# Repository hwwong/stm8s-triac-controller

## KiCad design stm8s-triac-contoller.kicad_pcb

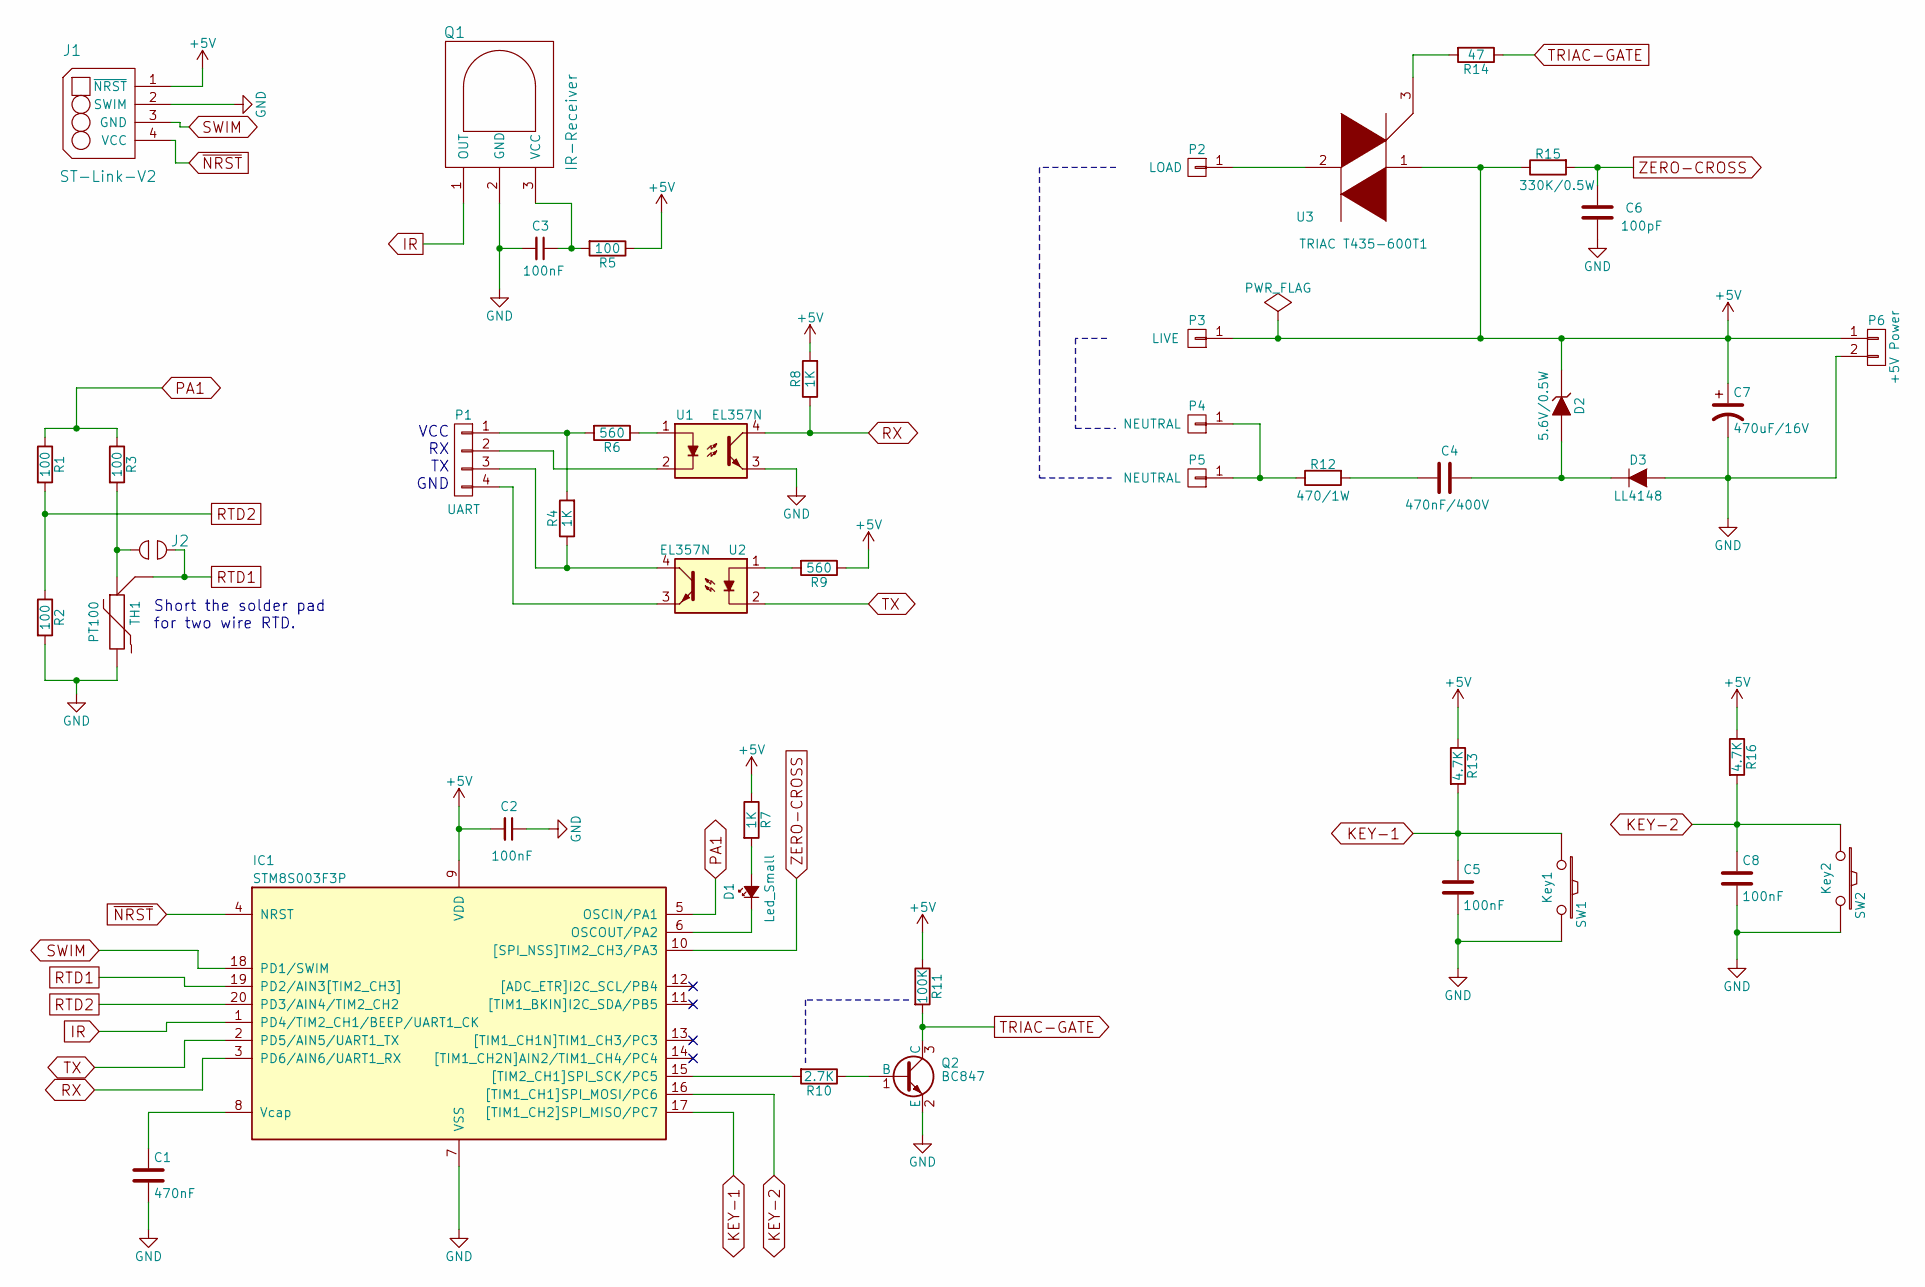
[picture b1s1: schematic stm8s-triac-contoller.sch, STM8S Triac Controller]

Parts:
C1: 470nF; C_0805
C2, C3, C5, C8: 100nF; C_0805
C4: 470nF/400V; C_Rect_L18_W11_H19_P15
C6: 100pF; C_0805
C7: 470uF/16V; C_Radial_D8_L11.5_P3.5
D1: Led_Small; LED-3MM
D2: 5.6V/0.5W; SOD-80
D3: LL4148; SOD-80
IC1: STM8S003F3P; TSSOP-20_4.4x6.5mm_Pitch0.65mm
J1: ST-Link-V2; Pin_Header_Straight_1x04
J2: Solder-Jumper-2; PAD-JUMPER-2-NO_YES_SILK
P1: UART; Pin_Header_Straight_1x04
P2: LOAD; SolderWirePad_single_1-2mmDrill
P3: LIVE; SolderWirePad_single_1-2mmDrill
P4, P5: NEUTRAL; SolderWirePad_single_1-2mmDrill
P6: +5V Power; Pin_Header_Straight_1x02
Q1: IR-Receiver; PNA460XM
Q2: BC847; SOT-23
R1, R2, R3, R5: 100; R_0805
R4, R7, R8: 1K; R_0805
R6, R9: 560; R_0805
R10: 2.7K; R_0805
R11: 100K; R_0805
R12: 470/1W; Resistor_Vertical_RM5mm
R13, R16: 4.7K; R_0805
R14: 47; R_0805
R15: 330K/0.5W; Resistor_Horizontal_RM10mm
SW1: Key1; TACTILE-PTH
SW2: Key2; TACTILE-PTH
TH1: PT100; TerminalBlock_Pheonix_MKDS1.5-3pol
U1, U2: EL357N; Optocoupler_SMD_HandSoldering_KPC357_LTV35x_PC357_SingleCha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
U3: TRIAC T435-600T1; TO-220_Neutral123_Vertical_LargePads

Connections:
+5V: C2.2, C7.1, D2.1 (K), IC1.9 (VDD), J1.1 (~NRST), P3.1, P6.1, R5.1, R7.1, R8.2, R9.1, R11.1, R13.1, R15.1, R16.1, U3.1
GND: C1.2, C2.1, C3.2, C5.2, C6.2, C7.2, C8.2, D3.2 (A), IC1.7 (VSS), J1.2 (SWIM), P6.2, Q1.2 (GND), Q2.2 (E), R2.2, SW1.2, SW2.2, TH1.3, U1.3
IR: IC1.1 (PD4/TIM2_CH1/BEEP/UART1_CK), Q1.1 (OUT)
KEY-1: C5.1, IC1.17 ([TIM1_CH2]SPI_MISO/PC7), R13.2, SW1.1
KEY-2: C8.1, IC1.16 ([TIM1_CH1]SPI_MOSI/PC6), R16.2, SW2.1
unnamed: C1.1, IC1.8 (Vcap)
unnamed: C3.1, Q1.3 (VCC), R5.2
unnamed: C4.1, D2.2 (A), D3.1 (K)
unnamed: C4.2, R12.2
unnamed: D1.1 (K), IC1.6 (OSCOUT/PA2)
unnamed: D1.2 (A), R7.2
unnamed: IC1.15 ([TIM2_CH1]SPI_SCK/PC5), R10.2
unnamed: J2.2, R3.2, TH1.2
unnamed: P1.1, R4.2, R6.2
unnamed: P1.2, U1.2
unnamed: P1.3, R4.1, U2.4
unnamed: P1.4, U2.3
unnamed: P2.1, U3.2
unnamed: P4.1, P5.1, R12.1
unnamed: Q2.1 (B), R10.1
unnamed: R6.1, U1.1
unnamed: R9.2, U2.1
unnamed: R14.2, U3.3
PA1: IC1.5 (OSCIN/PA1), R1.1, R3.1
RTD1: IC1.19 (PD2/AIN3[TIM2_CH3]), J2.1, TH1.1
RTD2: IC1.20 (PD3/AIN4/TIM2_CH2), R1.2, R2.1
RX: IC1.3 (PD6/AIN6/UART1_RX), R8.1, U1.4
SWIM: IC1.18 (PD1/SWIM), J1.3 (GND)
TRIAC-GATE: Q2.3 (C), R11.2, R14.1
TX: IC1.2 (PD5/AIN5/UART1_TX), U2.2
ZERO-CROSS: C6.1, IC1.10 ([SPI_NSS]TIM2_CH3/PA3), R15.2
~NRST: IC1.4 (NRST), J1.4 (VCC)

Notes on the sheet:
Short the solder pad for two wire RTD.
VCC RX TX GND

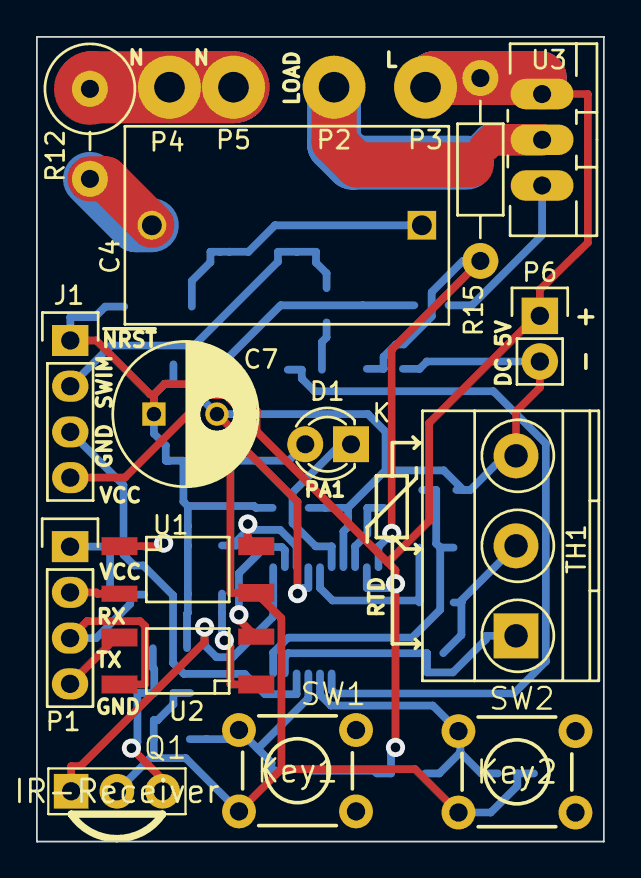
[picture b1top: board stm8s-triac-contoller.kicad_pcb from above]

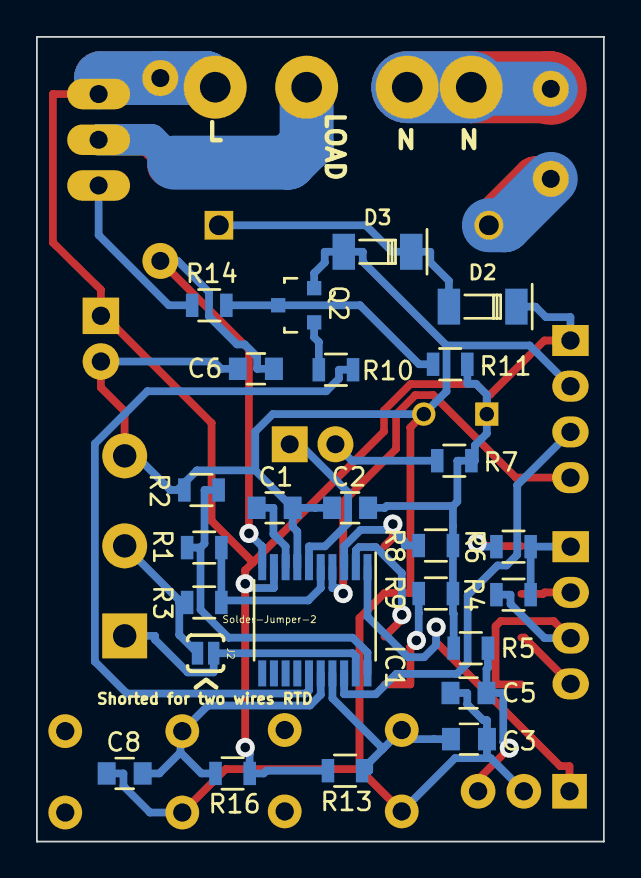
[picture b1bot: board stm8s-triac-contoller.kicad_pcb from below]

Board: 2 copper layers, 31.5 x 44.7 mm, 44 parts (25 on the bottom side), 32 nets.

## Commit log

2017-05-12 Added IAR IDE source code.
